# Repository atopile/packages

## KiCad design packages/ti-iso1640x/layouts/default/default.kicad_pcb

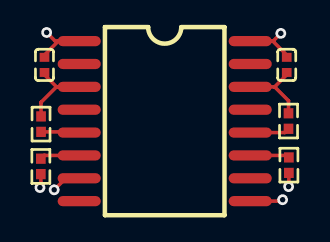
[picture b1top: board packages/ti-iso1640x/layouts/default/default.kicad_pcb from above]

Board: 2 copper layers, 7 parts (0 on the bottom side), 6 nets.

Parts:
C1, C2: 1±10.0%F; C0402
R1, R2, R3, R4: 10000±1.0%Ω; R0402
U1: SOIC-16_L10.3-W7.4-P1.27-LS10.3-BL

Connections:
SCL: R1.2, R2.2, U1.6, U1.11
SDA: R3.2, R4.2, U1.5, U1.12
decoupling_cap_side2-power-hv: C2.1, R2.1, R4.1, U1.14
decoupling_cap_side2-power-lv: C2.2, U1.9, U1.16
hv: C1.1, R1.1, R3.1, U1.3
lv: C1.2, U1.1, U1.7

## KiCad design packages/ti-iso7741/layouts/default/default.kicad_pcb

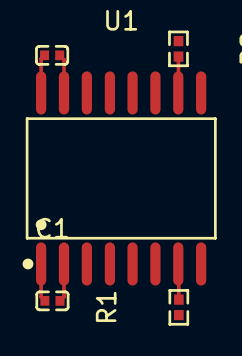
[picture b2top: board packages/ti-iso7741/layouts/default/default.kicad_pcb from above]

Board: 2 copper layers, 5 parts (0 on the bottom side), 6 nets.

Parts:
C1, C2: 0.0000001F; C0402
R1, R2: 10000Ω; R0402
U1: SOIC-16_L10.3-W7.5-P1.27-LS10.3-BL

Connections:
7: R1.2, U1.7
10: R2.2, U1.10
decap_side2-power-hv: C2.1, R2.1, U1.16
decap_side2-power-lv: C2.2, U1.9, U1.15
hv: C1.1, R1.1, U1.1
lv: C1.2, U1.2, U1.8

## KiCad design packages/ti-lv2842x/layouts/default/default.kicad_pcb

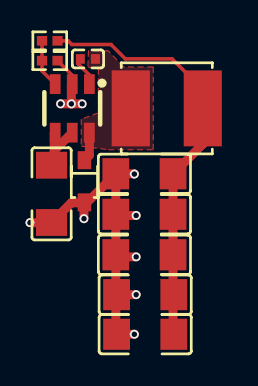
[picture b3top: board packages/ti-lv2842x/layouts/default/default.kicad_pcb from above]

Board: 2 copper layers, 12 parts (0 on the bottom side), 7 nets.

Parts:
C1: 470nF ±10%; C0402
C2: 4.7µF ±10%; C1206
C3, C4, C5, C6, C7: 10µF ±10%; C1206
D1: SOD-323_L1.8-W1.3-LS2.5-RD
L1: L 22µH ±20%; IND-SMD_L5.0-W5.0_H4.0
R1: 196kΩ ±1%; R0402
R2: 215kΩ ±1%; R0402
U1: SOT-23-6_L2.9-W1.6-P0.95-LS2.8-BR

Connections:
anode: C3.2, C4.2, C5.2, C6.2, C7.2, D1.2, R2.2
cathode: C1.2, D1.1, L1.1, U1.6
hv: C1.1, U1.1
input_cap-power-hv: C2.1, U1.4, U1.5
lv: C2.2, U1.2
output_caps[4]-power-hv: C3.1, C4.1, C5.1, C6.1, C7.1, L1.2, R1.1
ref_out-hv: R1.2, R2.1, U1.3
